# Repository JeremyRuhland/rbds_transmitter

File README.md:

RBDS Transmitter
----------------

Senior year project by Jeremy Ruhland, Spring 2014
Western Washington University, Electrical Engineering Technology

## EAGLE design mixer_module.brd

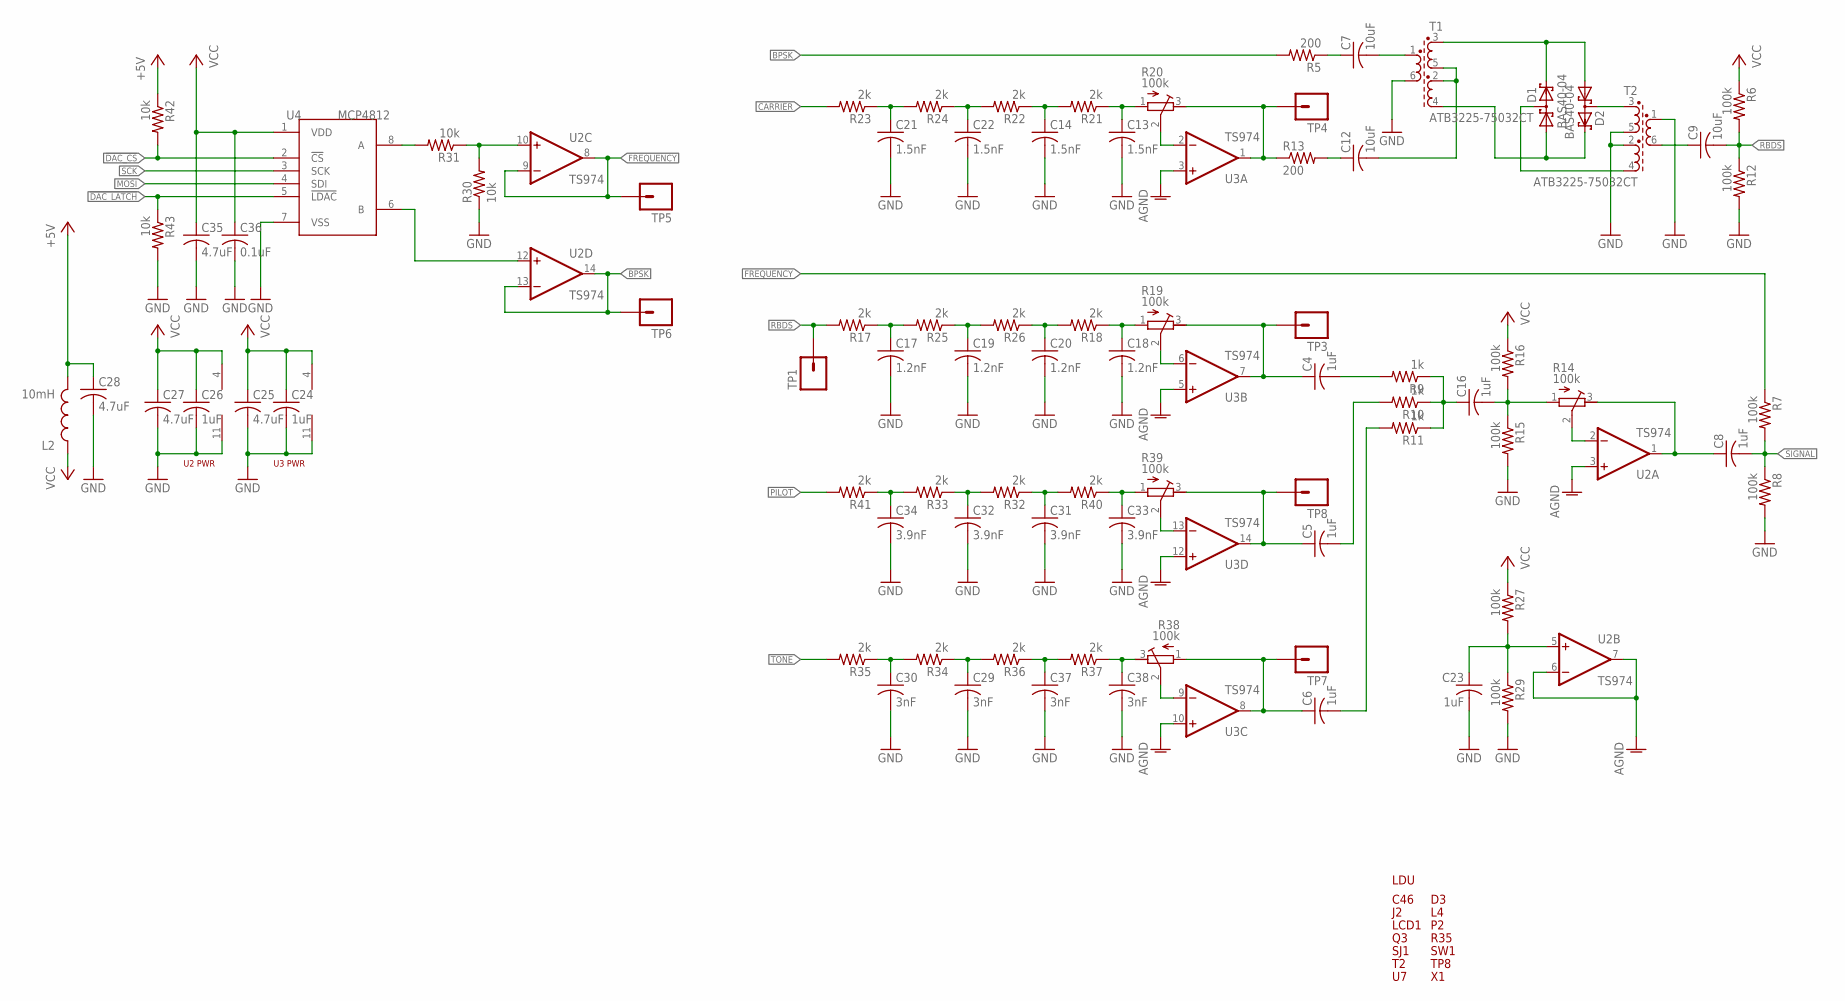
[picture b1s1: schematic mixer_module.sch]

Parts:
C4, C5, C6, C8, C16, C23, C24, C26: 1uF; C1206
C7, C9, C12: 10uF; C1206
C13, C14, C21, C22: 1.5nF; C1206
C17, C18, C19, C20: 1.2nF; C1206
C25, C27, C28, C35: 4.7uF; C1206
C29, C30, C37, C38: 3nF; C1206
C31, C32, C33, C34: 3.9nF; C1206
C36: 0.1uF; C1206
D1, D2: BAS40-04; SOT23
L2: 10mH; 1210
R5, R13: 200; R1206
R6, R7, R8, R12, R15, R16, R27, R29: 100k; R1206
R9, R10, R11: 1k; R1206
R14, R19, R20, R38, R39: 100k; RTRIM3304W
R17, R18, R21, R22, R23, R24, R25, R26, R32, R33, R34, R35, R36, R37, R40, R41: 2k; R1206
R30, R31, R42, R43: 10k; R1206
T1, T2: ATB3225-75032CT; TRANS
TP1, TP3, TP4, TP5, TP6, TP7, TP8: M01PTH; 1X01
U2, U3: TS974; SO14
U4: MCP4812; SO-08

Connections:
!DAC_CS: R42.2, U4.2 (!CS)
!DAC_LATCH: R43.1, U4.5 (!LDAC)
+5V: C28.1, L2.2, R42.1
AGND: U2.3 (+IN), U2.6 (-IN), U2.7 (OUT), U3.3 (+IN), U3.5 (+IN), U3.10 (+IN), U3.12 (+IN)
BPSK: R5.2, TP6.1, U2.13 (-IN), U2.14 (OUT)
CARRIER: R23.2
FREQUENCY: R7.1, TP5.1, U2.8 (OUT), U2.9 (-IN)
GND: C13.2, C14.2, C17.2, C18.2, C19.2, C20.2, C21.2, C22.2, C23.2, C24.2, C25.2, C26.2, C27.2, C28.2, C29.2, C30.2, C31.2, C32.2, C33.2, C34.2, C35.2, C36.2, C37.2, C38.2, R8.2, R12.2, R15.2, R29.2, R30.1, R43.2, T1.6, T2.1, T2.2, T2.5, U2.11 (V-), U3.11 (V-), U4.7 (VSS)
MOSI: U4.4 (SDI)
unnamed: C38.1, R37.1, R38.3 (E)
unnamed: D1.3 (C1A2), T2.4
unnamed: C16.2, R14.1 (A), R15.1, R16.2
unnamed: D2.3 (C1A2), T2.3
unnamed: D1.2 (C2), D2.1 (A1), T1.3
unnamed: D1.1 (A1), D2.2 (C2), T1.4
unnamed: C12.2, T1.2, T1.5
unnamed: C7.2, T1.1
unnamed: R14.2 (S), U2.2 (-IN)
unnamed: C8.1, R14.3 (E), U2.1 (OUT)
unnamed: C7.1, R5.1
unnamed: C12.1, R13.2
unnamed: R31.2, U4.8 (A)
unnamed: U2.12 (+IN), U4.6 (B)
unnamed: C9.1, T2.6
unnamed: R30.2, R31.1, U2.10 (+IN)
unnamed: C21.1, R23.1, R24.2
unnamed: C22.1, R22.2, R24.1
unnamed: C19.1, R25.1, R26.2
unnamed: C20.1, R18.2, R26.1
unnamed: C18.1, R18.1, R19.1 (A)
unnamed: C13.1, R20.1 (A), R21.1
unnamed: R19.2 (S), U3.6 (-IN)
unnamed: C4.1, R19.3 (E), TP3.1, U3.7 (OUT)
unnamed: C23.1, R27.2, R29.1, U2.5 (+IN)
unnamed: C32.1, R32.2, R33.1
unnamed: C31.1, R32.1, R40.2
unnamed: C33.1, R39.1 (A), R40.1
unnamed: R39.2 (S), U3.13 (-IN)
unnamed: C5.1, R39.3 (E), TP8.1, U3.14 (OUT)
unnamed: C29.1, R34.1, R36.2
unnamed: C37.1, R36.1, R37.2
unnamed: C6.1, R38.1 (A), TP7.1, U3.8 (OUT)
unnamed: R38.2 (S), U3.9 (-IN)
unnamed: R20.2 (S), U3.2 (-IN)
unnamed: C4.2, R9.2
unnamed: C5.2, R10.2
unnamed: C6.2, R11.2
unnamed: C16.1, R9.1, R10.1, R11.1
unnamed: R13.1, R20.3 (E), TP4.1, U3.1 (OUT)
unnamed: C17.1, R17.1, R25.2
unnamed: C34.1, R33.2, R41.1
unnamed: C30.1, R34.2, R35.1
unnamed: C14.1, R21.2, R22.1
PILOT: R41.2
RBDS: C9.2, R6.2, R12.1, R17.2, TP1.1
SCK: U4.3 (SCK)
SIGNAL: C8.2, R7.2, R8.1
TONE: R35.2
VCC: C24.1, C25.1, C26.1, C27.1, C35.1, C36.1, L2.1, R6.1, R16.1, R27.1, U2.4 (V+), U3.4 (V+), U4.1 (VDD)

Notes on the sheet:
LDU
C46
LCD1
R35
SJ1
TP8
SW1
U2 PWR
U3 PWR

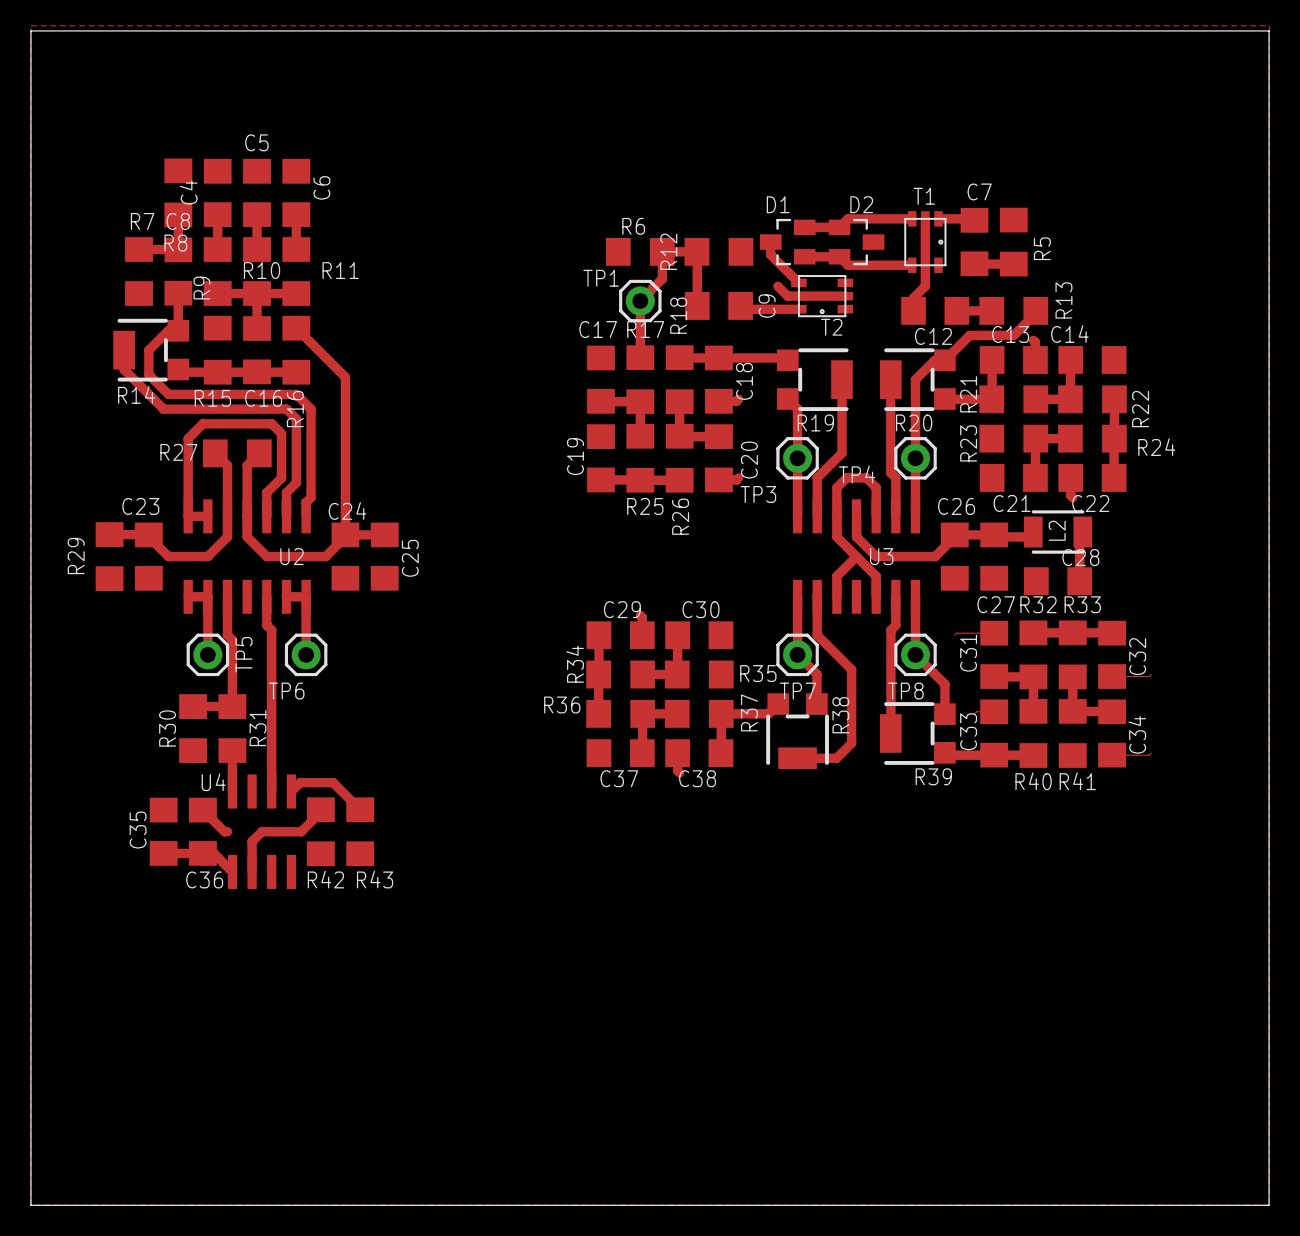
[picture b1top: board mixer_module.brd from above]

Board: 2 copper layers, 80.0 x 75.9 mm, 85 parts (0 on the bottom side), 54 nets.

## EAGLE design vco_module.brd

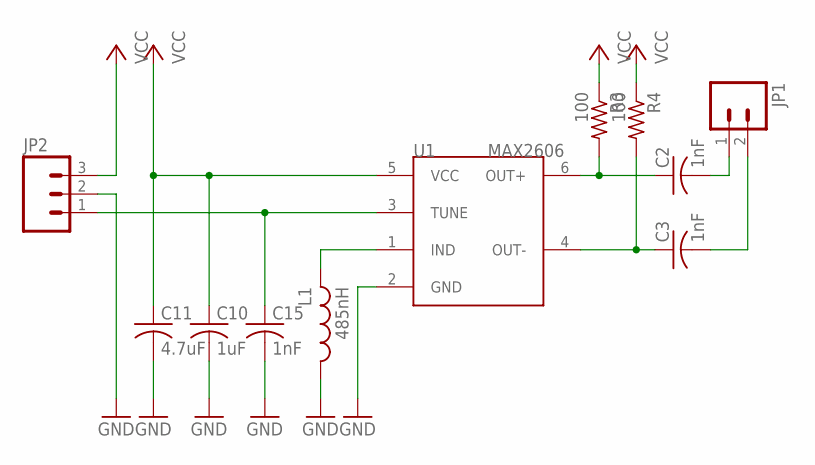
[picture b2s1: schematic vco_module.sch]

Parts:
C2, C3, C15: 1nF; C050-025X075
C10: 1uF; C050-025X075
C11: 4.7uF; C050-025X075
JP1: M023.5MM; SCREWTERMINAL-3.5MM-2
JP2: M03PTH; 1X03
L1: 485nH; 0204V
R3, R4: 100; 0207/10
U1: MAX2606; SOT23-6L

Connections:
GND: C10.2, C11.2, C15.2, JP2.2, L1.1, U1.2 (GND)
unnamed: L1.2, U1.1 (IND)
unnamed: C2.1, R3.2, U1.6 (OUT+)
unnamed: C3.1, R4.2, U1.4 (OUT-)
unnamed: C2.2, JP1.1
unnamed: C3.2, JP1.2
SIGNAL: C15.1, JP2.1, U1.3 (TUNE)
VCC: C10.1, C11.1, JP2.3, R3.1, R4.1, U1.5 (VCC)

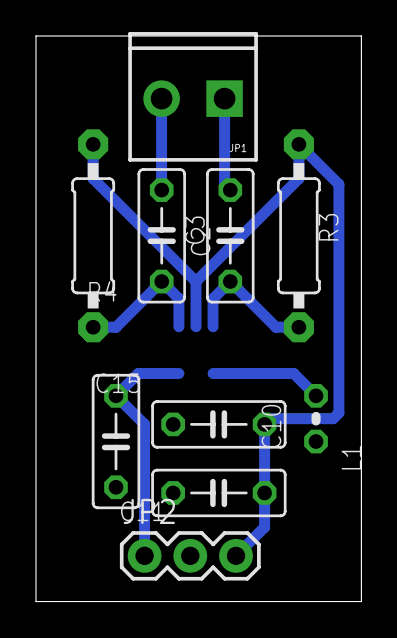
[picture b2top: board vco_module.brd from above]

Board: 2 copper layers, 18.1 x 31.4 mm, 11 parts (1 on the bottom side), 8 nets.

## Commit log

2014-04-08 added gitignore
2014-04-08 begun laying out circuit, uC & battery charger
2014-04-09 added switching regulator
2014-04-09 added datasheets
2014-04-09 added dac, finished regulator
2014-04-09 wiring up dac
2014-04-10 added diode ring mixer
2014-04-12 opamps
2014-04-12 adding summing amp
2014-04-14 added low pass filter
2014-04-14 adding low pass for pilot tones
2014-04-17 didn't really actually work after class
2014-04-19 adding filters for pilot/sound
2014-04-20 more filters
2014-04-20 yet more filters
2014-04-22 seperated out some parts
2014-04-24 fixed up usb charger for load switching, worked some on op amps
2014-04-25 still working
2014-04-27 adding tx
2014-04-27 added vco datasheet
2014-04-28 rebuilding filter systems
2014-04-28 need to wire subsystems to mcu
2014-04-29 added datasheets for more comps
2014-04-29 finished prelim layout
2014-04-29 finsihed
2014-05-01 final design tweaks for hardware descript
2014-05-01 added value to r15, erexported
2014-05-04 added bom
2014-05-05 added more part nums
2014-05-05 another bom entry
2014-05-06 found all components
2014-05-11 layed out some power components
2014-05-14 working
2014-05-15 schematic update: corrected 5v connection
2014-05-20 changed transformer layout
2014-05-20 layed out some more traces
2014-05-22 swapped u3c and u3d
2014-05-23 wiring up modules
2014-05-24 changed mcu agnd to gnd: request engineering change form
2014-05-24 few more airwires
2014-05-24 renubmered everything, request engineering change forum
2014-05-24 board ready for gerbering
2014-05-24 added silkscreens
2014-05-24 last minutes changes, board finalized
2014-05-24 first commit of code
2014-05-25 fleshing out code, control loop states
2014-05-25 setting up gpio init
2014-05-25 working on frequency input
2014-05-25 working on lcd
2014-05-26 adding lcd custom char, working on frequency input
2014-05-26 working on data entry state
2014-05-26 undid small change to location of frequency info buffer
2014-05-26 removed unneeded spi function
2014-05-26 making huge numbers of bitfield structs
2014-05-26 fixed spi code for writing to dac
2014-05-26 moved includes around for dependency reasons
2014-05-26 fixing up spi for dac control
2014-05-26 correcting array referencing
2014-05-27 created crc module
2014-05-27 heavy work on data and encode tasks, force buffer to be even packet lengths
2014-05-27 corrected group type error, cd to b
2014-05-27 corrected array error
2014-05-27 corrected a few variable errors, code compiles now
2014-05-28 working on enc function bit manipulation
2014-05-28 possibly finished encoding function
2014-05-28 added dummy sintable vars
2014-05-28 finished program skeleton, add in transmit frequenct calculations, crc function
2014-05-28 corrected spelling mistake bin to bit
2014-05-28 crc is probably wrong still
2014-05-28 crc module now working
2014-05-28 corrected end of msg by adding return char and new packets as nessesary
2014-05-29 working on pwm
2014-05-29 turn off some unwanted modules
2014-05-29 engineering change request form: swapped pd6 and pb1
2014-05-29 engineering change request form: swapped pd6 and pb1, reexported files
2014-05-29 swapped to new dac latch port
2014-05-29 pwm inits written, power control written
2014-05-29 finished writing routines
2014-05-29 updated sin table with proper bits for dac
2014-05-29 added missing semicolon
2014-05-29 added comments on transmit task
2014-05-29 making some code corrections
2014-05-31 starting to split up board into smaller millable boards
2014-06-02 transfering over to morton's lcd lib
2014-06-02 still getting lcd to work
2014-06-02 reworked from oneil's lcd lib
2014-06-03 lcd modules now working
2014-06-03 fixed make file issue
2014-06-03 fixed up code, proper pwm working
2014-06-04 updated pdf
2014-06-04 fixed for boardmill
2014-06-05 final changes to code
2014-06-05 final changes to unused external boards
2014-06-05 added firmware zip

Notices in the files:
parts and their libraries:
sparkfun: Licensing: CC v3.0 Share-Alike You are welcome to use this library for commercial purposes.
